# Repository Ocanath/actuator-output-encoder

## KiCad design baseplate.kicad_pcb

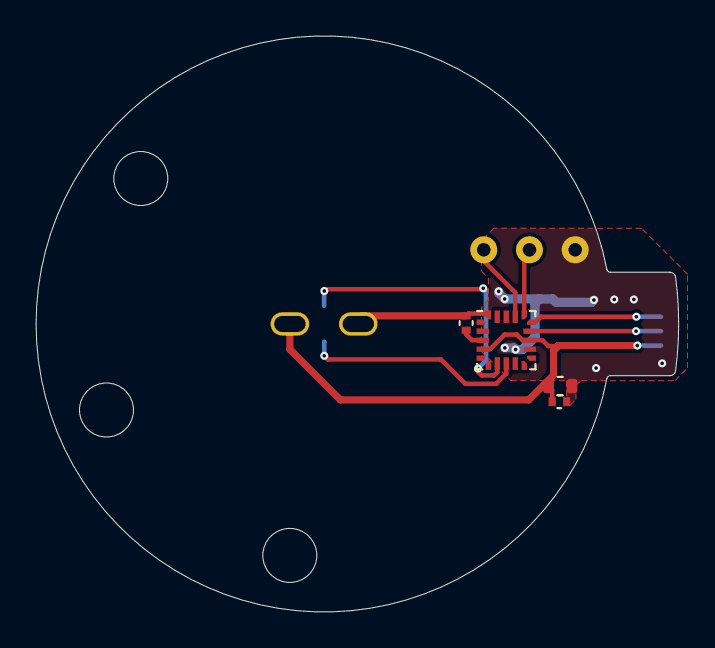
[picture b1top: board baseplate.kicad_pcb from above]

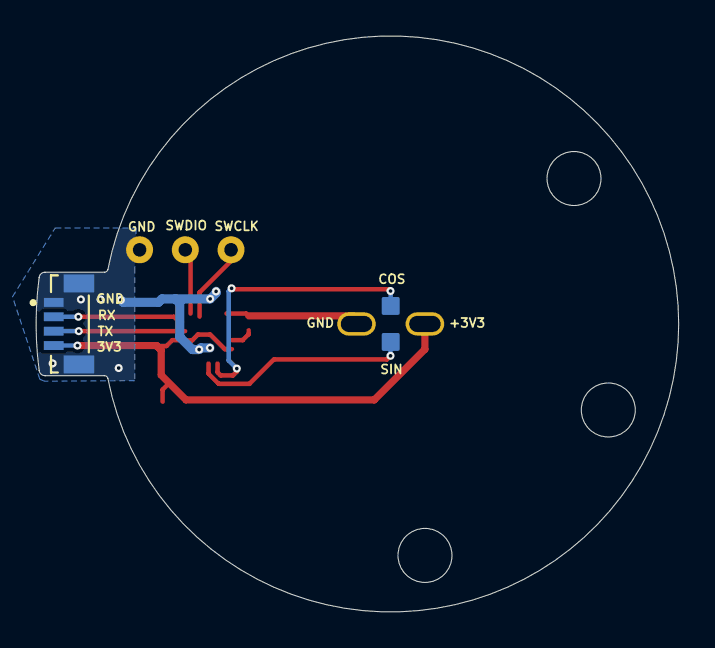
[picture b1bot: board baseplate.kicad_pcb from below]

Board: 2 copper layers, 35.7 x 32.0 mm, 16 parts (3 on the bottom side), 9 nets.

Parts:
C1: 100nF; C_0402_1005Metric
C2: 100nF 0402; C_0402_1005Metric
C4: 4.7nF 0603; C_0603_1608Metric
J1: 10144042-04011LF; AMPHENOL_10144042-04011LF
M1, M4, M100000: THRU_HOLE_PAD; dogbone_slot
M2, M3: THRU_HOLE_PAD; dogbone_pad
M5, M6, M7: THRU_HOLE_PAD; PAD-BREADBOARD
M8, M9, M10: THRU_HOLE_PAD; MountingHole3mm
U1: STM32L011F4Ux; ST_UFQFPN-20_3x3mm_P0.5mm

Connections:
+3V3: C2.1, C4.1, J1.4, M1.1, U1.4 (VDDA), U1.13 (VDD)
/COS: M2.1, U1.7 (PA4)
/RX: J1.2, U1.15 (PA10)
/SIN: M3.1, U1.8 (PA5)
/SWCLK: M6.1, U1.17 (PA14)
/SWDIO: M5.1, U1.16 (PA13)
/TX: J1.3, U1.14 (PA9)
GND: C1.2, C2.2, C4.2, J1.1, J1.S1, J1.S2, M4.1, M7.1, U1.12 (VSS), U1.20 (PB9)
unnamed: C1.1, U1.3 (NRST)

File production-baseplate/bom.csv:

Designator,Footprint,Quantity,Value,LCSC Part #
C1,0402,1,100nF,
C2,0402,1,100nF 0402,
C4,0603,1,4.7nF 0603,
J1,AMPHENOL_10144042-04011LF,1,10144042-04011LF,
U1,ST_UFQFPN-20_3x3mm_P0.5mm,1,STM32L011F4Ux,

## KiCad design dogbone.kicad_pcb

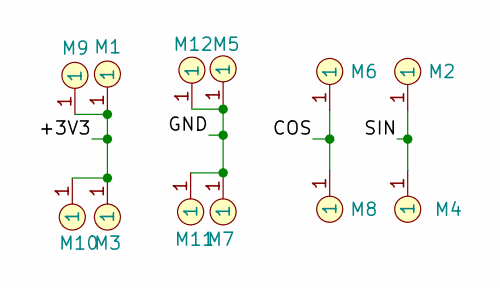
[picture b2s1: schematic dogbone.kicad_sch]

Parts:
M1, M2, M3, M4, M5, M6, M7, M8, M9, M10, M11, M12: THRU_HOLE_PAD; dogbone_pad

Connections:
/+3V3: M1.1, M3.1, M9.1, M10.1
/COS: M6.1, M8.1
/GND: M5.1, M7.1, M11.1, M12.1
/SIN: M2.1, M4.1

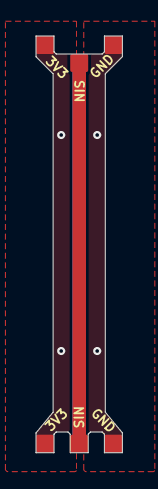
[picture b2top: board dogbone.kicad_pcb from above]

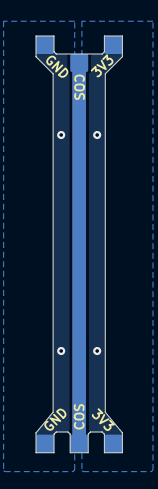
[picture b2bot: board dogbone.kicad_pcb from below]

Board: 2 copper layers, 4.8 x 23.1 mm, 12 parts (6 on the bottom side), 4 nets.

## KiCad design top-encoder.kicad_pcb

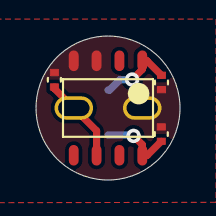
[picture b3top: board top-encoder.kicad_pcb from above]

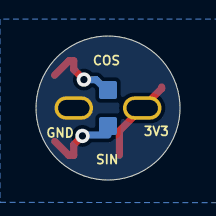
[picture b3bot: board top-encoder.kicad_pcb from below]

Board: 2 copper layers, 8.0 x 8.0 mm, 8 parts (2 on the bottom side), 4 nets.

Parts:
C1, C2, C3: 100nF; C_0402_1005Metric
M1, M4: THRU_HOLE_PAD; dogbone_slot
M2, M3: THRU_HOLE_PAD; dogbone_pad
U2: TLE5009E1000FUMA1; SOIC8-TLE5009

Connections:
/3v3: C1.1, M1.1, U2.6 (Vdd)
/COS: C2.1, M2.1, U2.1 (COS_P)
/SIN: C3.1, M3.1, U2.8 (SIN_P)
GND: C1.2, C2.2, C3.2, M4.1, U2.3 (GND2), U2.4 (GND1)

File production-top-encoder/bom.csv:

Designator,Footprint,Quantity,Value,LCSC Part #
"C1, C2, C3",0402,3,100nF,
U2,SOIC8-TLE5009,1,TLE5009E1000FUMA1,

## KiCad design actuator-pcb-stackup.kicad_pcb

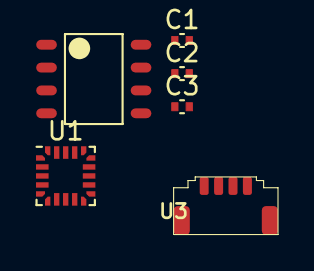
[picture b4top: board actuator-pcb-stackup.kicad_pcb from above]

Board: 2 copper layers, 6 parts (0 on the bottom side), 7 nets, no tracks yet.

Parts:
C1, C2, C3: 100nF; C_0402_1005Metric
U1: STM32L011F4Ux; ST_UFQFPN-20_3x3mm_P0.5mm
U2: TLE5009E1000FUMA1; SOIC8-TLE5009
U3: DF52-4S-0.8H(21)

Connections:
/3v3: U1.4 (VDDA), U1.13 (VDD), U2.6 (Vdd)
/COS: C2.1, U1.8 (PA5), U2.1 (COS_P)
/RX: U1.15 (PA10), U3.3
/SIN: C3.1, U1.7 (PA4), U2.8 (SIN_P)
/TX: U1.14 (PA9), U3.2
GND: C1.2, C2.2, C3.2, U1.12 (VSS), U1.20 (PB9), U2.3 (GND2), U2.4 (GND1), U3.4, U3.5 (MNT), U3.6 (MNT)
unnamed: C1.1, U1.3 (NRST)

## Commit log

2024-03-08 init commit
2024-03-08 renamed proj and checked it, working
2024-03-08 dogBONE
2024-03-08 dxfs copied over, baseplate pcb fully designed, more lib management
2024-03-08 designed dogbone
2024-03-08 net labelling, silkscreen, boards finished
2024-03-08 changed plot settings
2024-03-08 changed dxf export settings for baseplate. added silk to the encoder portion
2024-03-08 dxf export settings
2024-03-08 updated pad spacing for 1mm for dogbone and baseplate
2024-03-08 step files from freecad, put the connector on the baseplate on the bottom of the baseplate
2024-03-08 gitignore dxf
2024-03-12 reverted baseplate back to all on top, designed to flip over, and solder from the component side. dogbone bottom changed so one end has three prongs
2024-03-13 updated baseplate dsign
2024-03-26 gerbers
2024-03-26 board auto-panelized;
2024-03-26 panelization options
2024-04-02 mounting holes
